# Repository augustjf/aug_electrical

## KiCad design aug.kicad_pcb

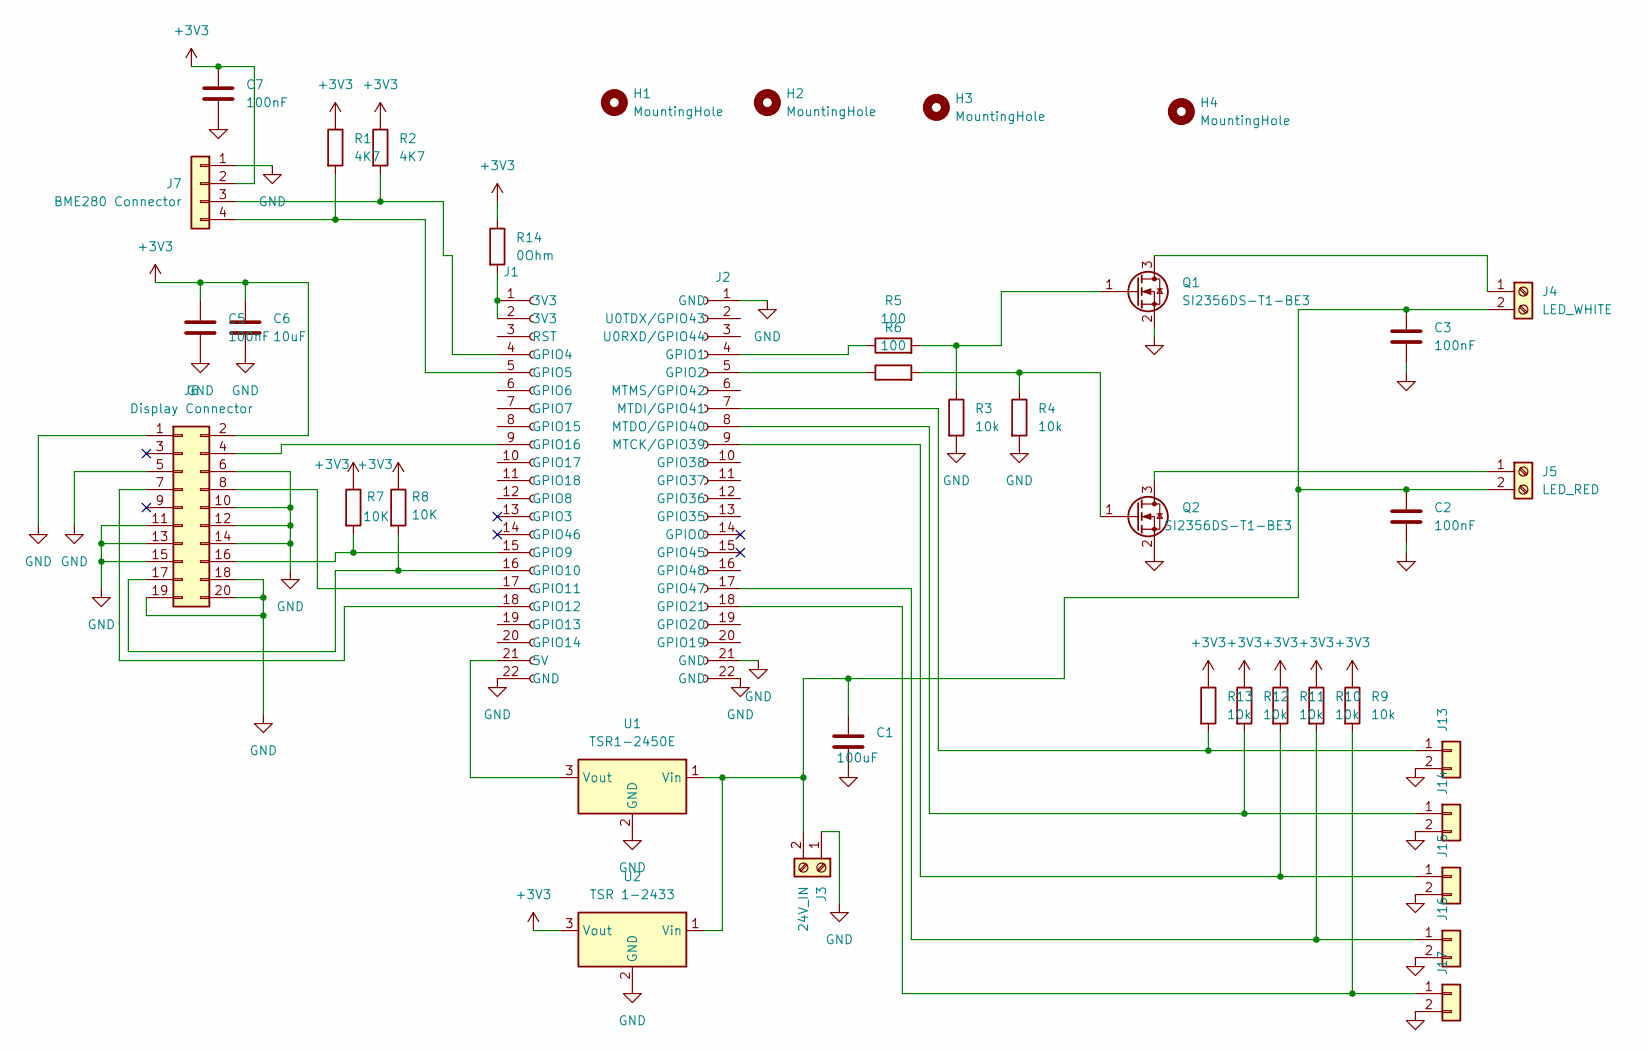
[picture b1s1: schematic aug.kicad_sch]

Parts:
C1: 100uF; C_Disc_D10.5mm_W5.0mm_P5.00mm
C2, C3, C5, C7: 100nF; C_0805_2012Metric
C6: 10uF; C_Rect_L4.0mm_W2.5mm_P2.50mm
H1, H2, H3, H4: MountingHole; MountingHole_3.2mm_M3
J1, J2: Conn_01x22_Socket; PinSocket_1x22_P2.54mm_Vertical
J3: 24V_IN; TerminalBlock_CUI_TB007-508-02_1x02_P5.08mm_Horizontal
J4: LED_WHITE; TerminalBlock_CUI_TB007-508-02_1x02_P5.08mm_Horizontal
J5: LED_RED; TerminalBlock_CUI_TB007-508-02_1x02_P5.08mm_Horizontal
J6: Display Connector; PinHeader_2x10_P2.54mm_Vertical
J7: BME280 Connector; PinHeader_1x04_P2.54mm_Vertical
J13, J14, J15, J16, J17: Conn_01x02; PinHeader_1x02_P2.54mm_Vertical
Q1, Q2: SI2356DS-T1-BE3; SOT-23
R1, R2: 4K7; R_0805_2012Metric
R3, R4, R9, R10, R11, R12, R13: 10k; R_0805_2012Metric
R5, R6: 100; R_0805_2012Metric
R7, R8: 10K; R_0805_2012Metric
R14: 0Ohm; R_0805_2012Metric
U1: TSR1-2450E; Converter_DCDC_TRACO_TSR1-xxxxE_THT
U2: TSR 1-2433; Converter_DCDC_TRACO_TSR1-xxxxE_THT

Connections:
+3V3: C5.1, C6.1, C7.1, J6.2 (3v3), J7.2 (3v3), R1.1, R2.1, R7.1, R8.1, R9.1, R10.1, R11.1, R12.1, R13.1, R14.1, U2.3 (Vout)
GND: C1.2, C2.2, C3.2, C5.2, C6.2, C7.2, J1.22 (GND), J2.1 (GND), J2.21 (GND), J2.22 (GND), J3.1, J6.1 (GND), J6.5 (GND), J6.6 (GND), J6.10 (GND), J6.11 (GND), J6.12 (GND), J6.13 (GND), J6.14 (GND), J6.15 (GND), J6.18 (GND), J6.19 (BS1), J6.20 (BS0), J7.1 (GND), J13.2, J14.2, J15.2, J16.2, J17.2, Q1.2 (S), Q2.2 (S), R3.2, R4.2, U1.2 (GND), U2.2 (GND)
unnamed: J1.1 (3V3), J1.2 (3V3), R14.2
unnamed: J1.21 (5V), U1.3 (Vout)
unnamed: J1.4 (GPIO4), J7.3 (SDA), R2.2
unnamed: J1.5 (GPIO5), J7.4 (SCL), R1.2
unnamed: J1.15 (GPIO9), J6.16 (!RES), R7.2
unnamed: J1.16 (GPIO10), J6.17 (!CS), R8.2
unnamed: J1.17 (GPIO11), J6.8 (SDIN)
unnamed: J1.18 (GPIO12), J6.7 (SCLK)
unnamed: J1.9 (GPIO16), J6.4 (D/C)
unnamed: J2.4 (GPIO1), R5.1
unnamed: J2.5 (GPIO2), R6.1
unnamed: C1.1, C2.1, C3.1, J3.2, J4.2, J5.2, U1.1 (Vin), U2.1 (Vin)
unnamed: J4.1, Q1.3 (D)
unnamed: J5.1, Q2.3 (D)
unnamed: J2.7 (MTDI/GPIO41), J13.1, R13.2
unnamed: J2.8 (MTDO/GPIO40), J14.1, R12.2
unnamed: J2.9 (MTCK/GPIO39), J15.1, R11.2
unnamed: J2.17 (GPIO47), J16.1, R10.2
unnamed: J2.18 (GPIO21), J17.1, R9.2
unnamed: Q1.1 (G), R3.1, R5.2
unnamed: Q2.1 (G), R4.1, R6.2

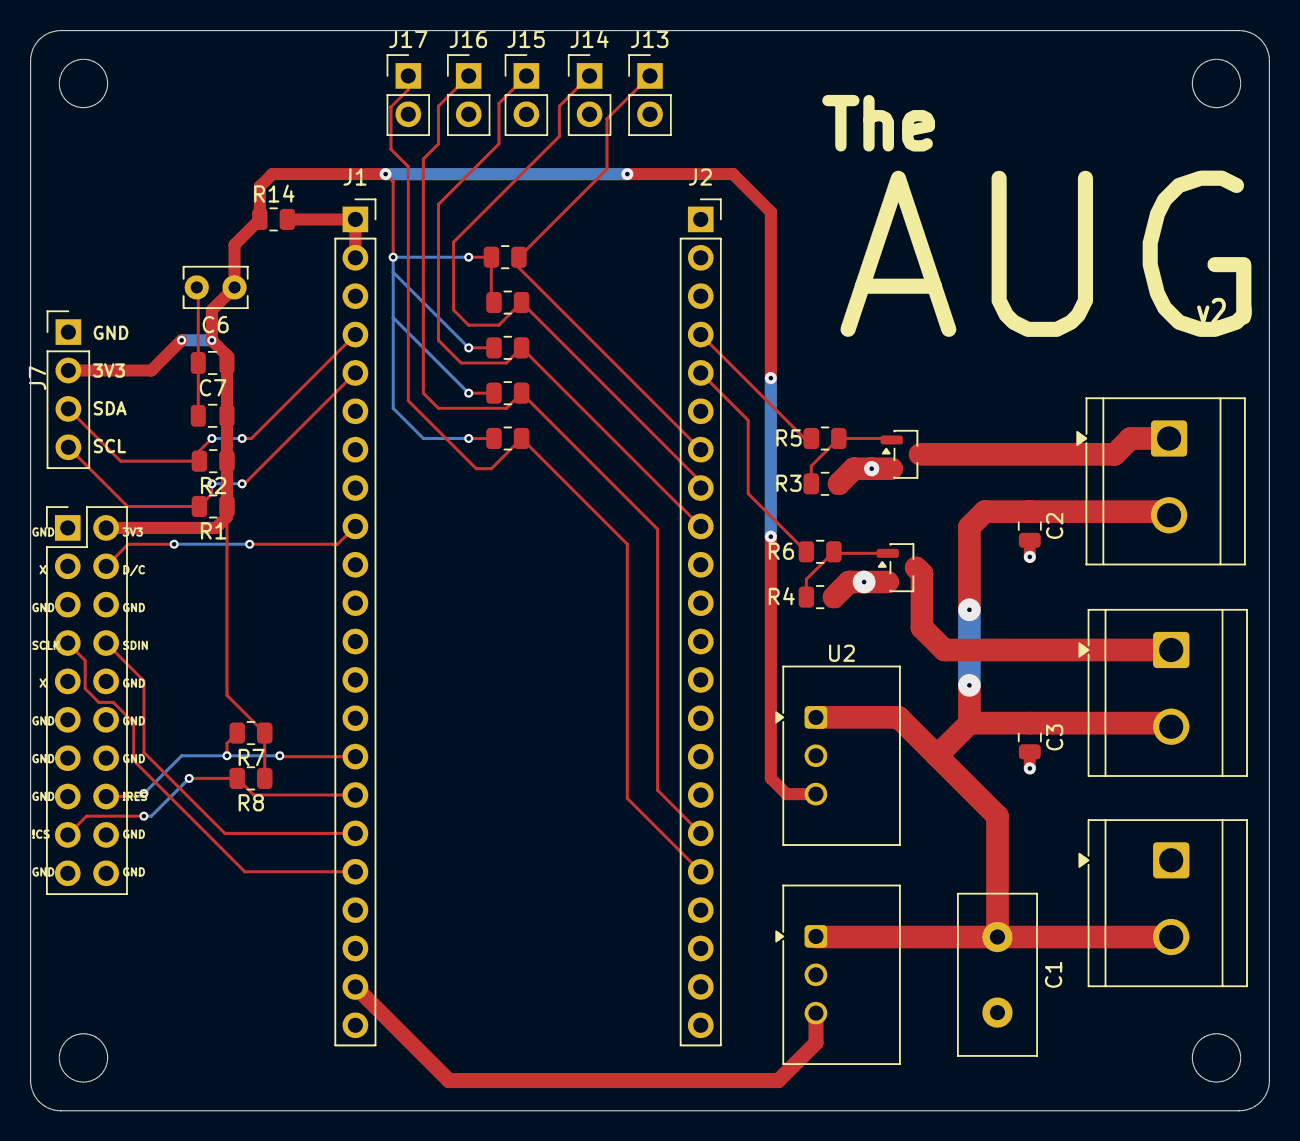
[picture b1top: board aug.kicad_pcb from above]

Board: 2 copper layers, 82.0 x 71.5 mm, 40 parts (0 on the bottom side), 23 nets.
